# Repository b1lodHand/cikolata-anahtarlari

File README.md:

# cikolata anahtarlari
 cikulatli anahtarlar :d

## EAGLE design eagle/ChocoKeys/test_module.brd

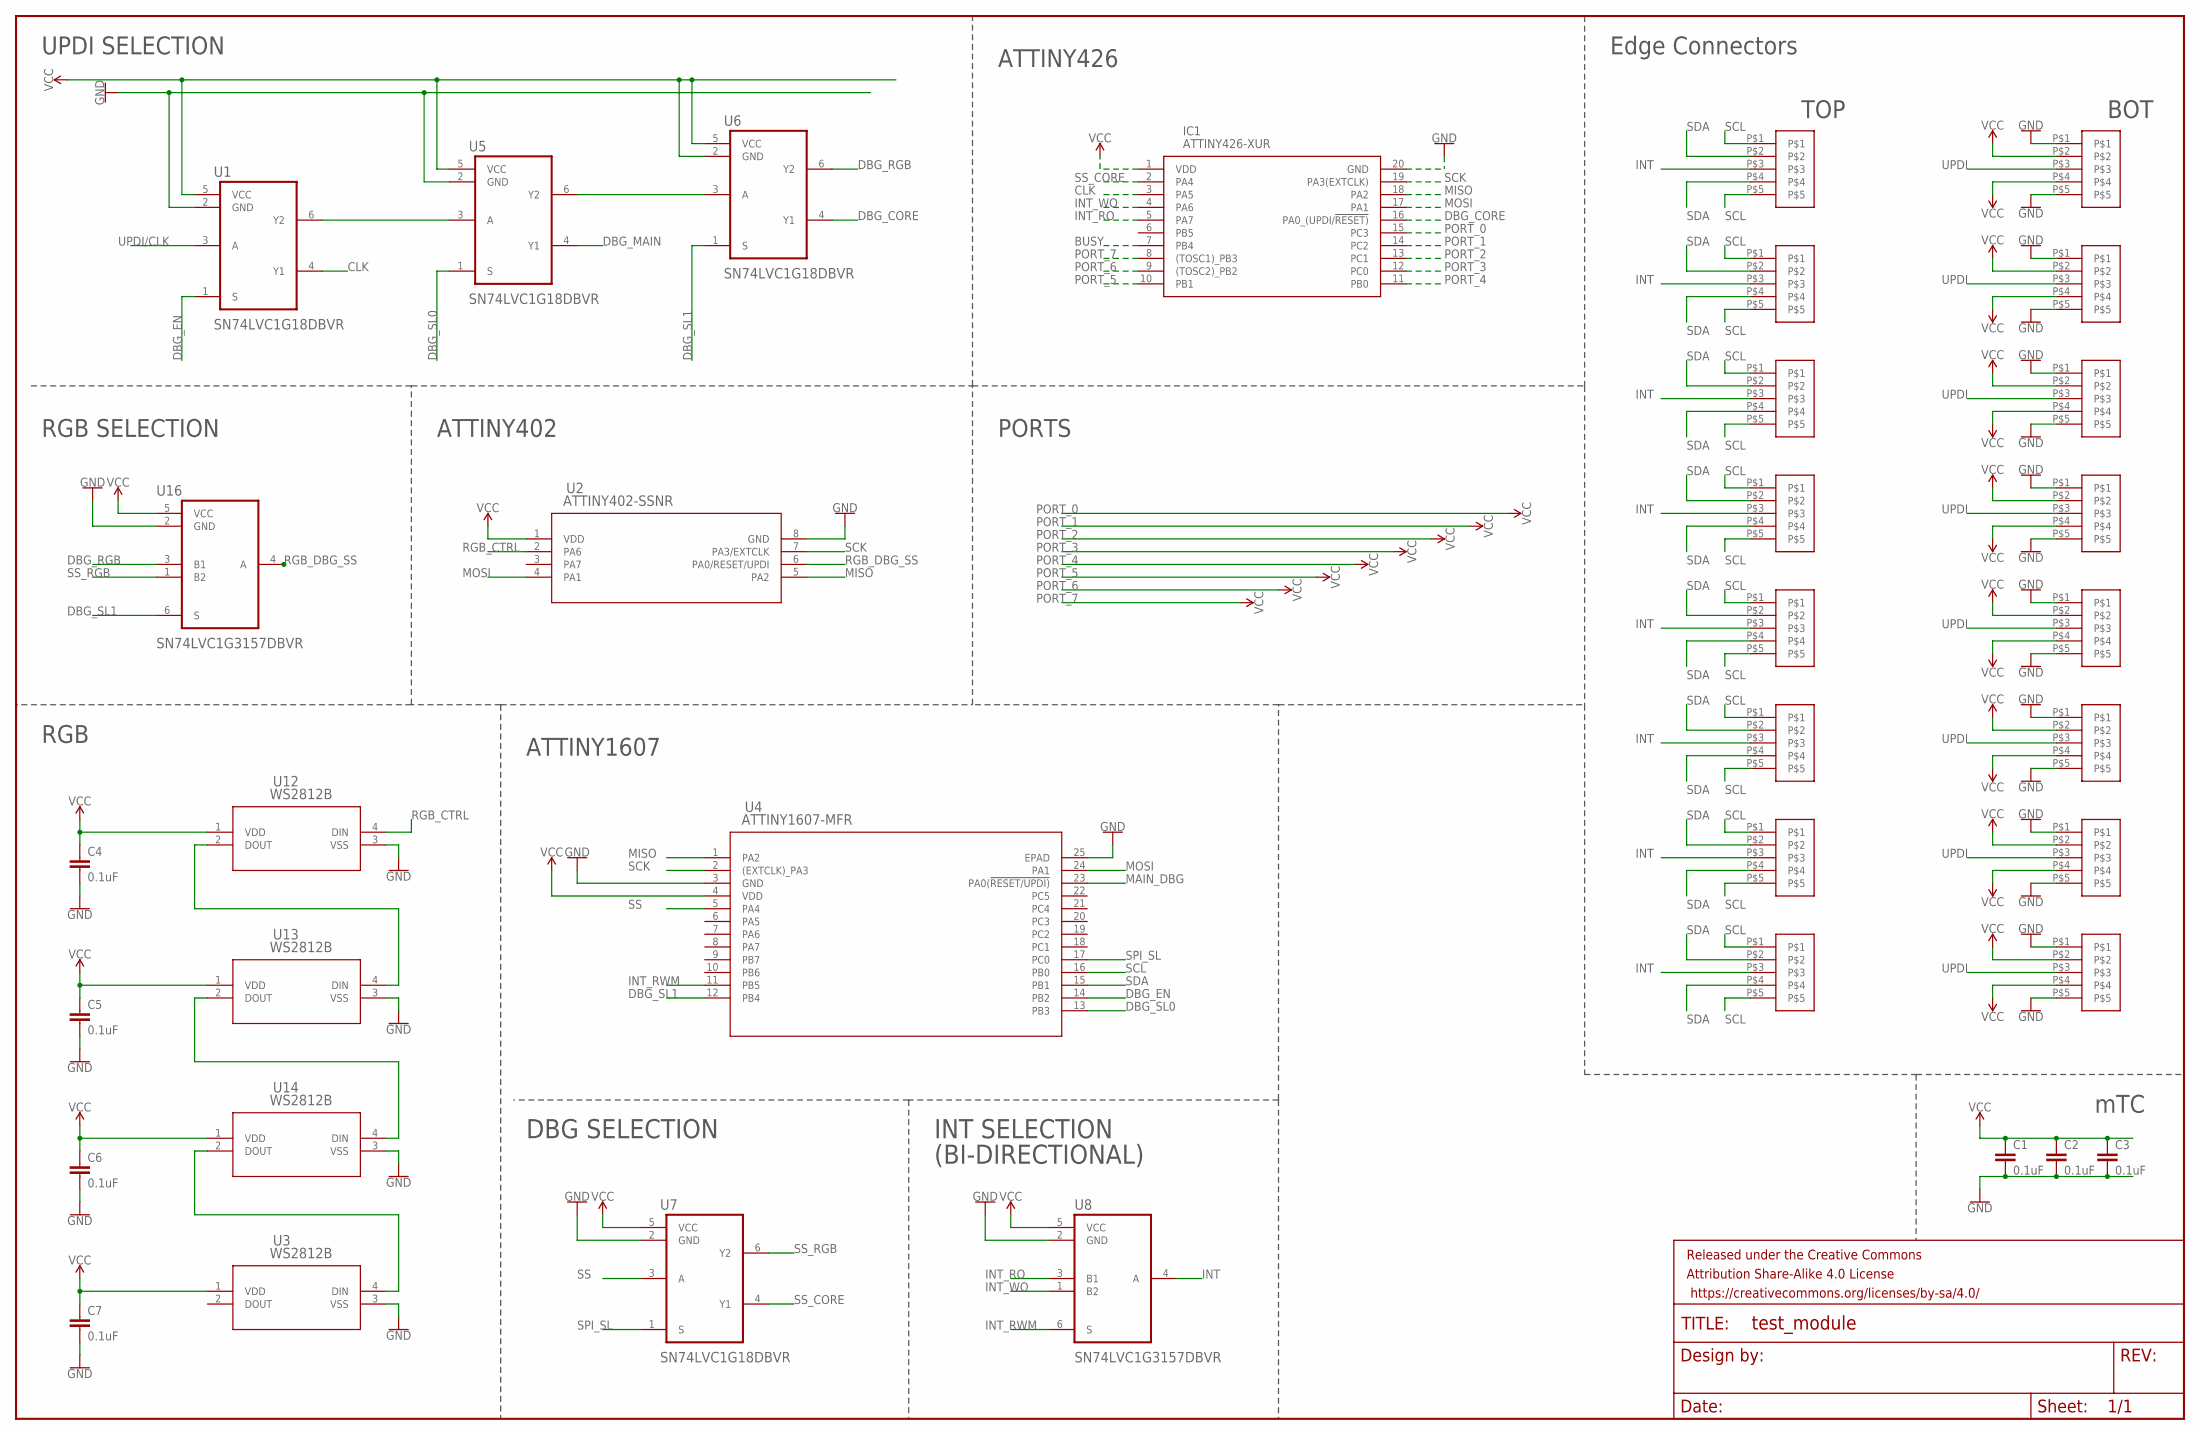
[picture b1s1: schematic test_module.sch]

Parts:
C1, C2, C3, C4, C5, C6, C7: 0.1uF; 0603
E1, E2, E3, E4, E5, E6, E7, E8, E9, E10, E11, E12, E13, E14, E15, E16: 5-PIN-EDGE-CONNECTOR
FRAME1: FRAME-LEDGER; CREATIVE_COMMONS
IC1: ATTINY426-XUR; SOP65P780X200-20N
U1, U5, U6, U7: SN74LVC1G18DBVR; SOT95P280X145-6N
U2: ATTINY402-SSNR; SOIC8_4P9X3P9MC_MCH
U3, U12, U13, U14: WS2812B; WS2812B_WDS
U4: ATTINY1607-MFR; QFN24_4X4_MCH
U8, U16: SN74LVC1G3157DBVR; SOT95P280X145-6N

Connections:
BUSY: IC1.7 (PB4)
CLK: IC1.3 (PA5), U1.4 (Y1)
DBG_CORE: IC1.16 (PA0_(UPDI/!RESET)), U6.4 (Y1)
DBG_EN: U1.1 (S), U4.14 (PB2)
DBG_MAIN: U5.4 (Y1)
DBG_RGB: U6.6 (Y2), U16.3 (B1)
DBG_SL0: U4.13 (PB3), U5.1 (S)
DBG_SL1: U4.12 (PB4), U6.1 (S), U16.6 (S)
GND: C1.2, C2.2, C3.2, C4.2, C5.2, C6.2, C7.2, E5.P$1, E5.P$5, E6.P$1, E6.P$5, E7.P$1, E7.P$5, E8.P$1, E8.P$5, E9.P$1, E9.P$5, E10.P$1, E10.P$5, E11.P$1, E11.P$5, E12.P$1, E12.P$5, IC1.20 (GND), U1.2 (GND), U2.8 (GND), U3.3 (VSS), U4.3 (GND), U4.25 (EPAD), U5.2 (GND), U7.2 (GND), U8.2 (GND), U12.3 (VSS), U13.3 (VSS), U14.3 (VSS), U16.2 (GND)
INT: E1.P$3, E2.P$3, E3.P$3, E4.P$3, E13.P$3, E14.P$3, E15.P$3, E16.P$3, U8.4 (A)
INT_RO: IC1.5 (PA7), U8.3 (B1)
INT_RWM: U4.11 (PB5), U8.6 (S)
INT_WO: IC1.4 (PA6), U8.1 (B2)
MAIN_DBG: U4.23 (PA0(!RESET/UPDI))
MISO: IC1.18 (PA2), U2.5 (PA2), U4.1 (PA2)
MOSI: IC1.17 (PA1), U2.4 (PA1), U4.24 (PA1)
unnamed: U12.2 (DOUT), U13.4 (DIN)
unnamed: U13.2 (DOUT), U14.4 (DIN)
unnamed: U3.4 (DIN), U14.2 (DOUT)
unnamed: U1.6 (Y2), U5.3 (A)
unnamed: U5.6 (Y2), U6.3 (A)
PORT_0: IC1.15 (PC3)
PORT_1: IC1.14 (PC2)
PORT_2: IC1.13 (PC1)
PORT_3: IC1.12 (PC0)
PORT_4: IC1.11 (PB0)
PORT_5: IC1.10 (PB1)
PORT_6: IC1.9 ((TOSC2)_PB2)
PORT_7: IC1.8 ((TOSC1)_PB3)
RGB_CTRL: U2.2 (PA6), U12.4 (DIN)
RGB_DBG_SS: U2.6 (PA0/RESET/UPDI), U16.4 (A)
SCK: IC1.19 (PA3(EXTCLK)), U2.7 (PA3/EXTCLK), U4.2 ((EXTCLK)_PA3)
SCL: E1.P$1, E1.P$5, E2.P$1, E2.P$5, E3.P$1, E3.P$5, E4.P$1, E4.P$5, E13.P$1, E13.P$5, E14.P$1, E14.P$5, E15.P$1, E15.P$5, E16.P$1, E16.P$5, U4.16 (PB0)
SDA: E1.P$2, E1.P$4, E2.P$2, E2.P$4, E3.P$2, E3.P$4, E4.P$2, E4.P$4, E13.P$2, E13.P$4, E14.P$2, E14.P$4, E15.P$2, E15.P$4, E16.P$2, E16.P$4, U4.15 (PB1)
SPI_SL: U4.17 (PC0), U7.1 (S)
SS: U4.5 (PA4), U7.3 (A)
SS_CORE: IC1.2 (PA4), U7.4 (Y1)
SS_RGB: U7.6 (Y2), U16.1 (B2)
UPDI: E5.P$3, E6.P$3, E7.P$3, E8.P$3, E9.P$3, E10.P$3, E11.P$3, E12.P$3
UPDI/CLK: U1.3 (A)
VCC: C1.1, C2.1, C3.1, C4.1, C5.1, C6.1, C7.1, E5.P$2, E5.P$4, E6.P$2, E6.P$4, E7.P$2, E7.P$4, E8.P$2, E8.P$4, E9.P$2, E9.P$4, E10.P$2, E10.P$4, E11.P$2, E11.P$4, E12.P$2, E12.P$4, IC1.1 (VDD), U1.5 (VCC), U2.1 (VDD), U3.1 (VDD), U4.4 (VDD), U5.5 (VCC), U6.2 (GND), U6.5 (VCC), U7.5 (VCC), U8.5 (VCC), U12.1 (VDD), U13.1 (VDD), U14.1 (VDD), U16.5 (VCC)

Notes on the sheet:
mTC
TOP
BOT
Edge Connectors
RGB
UPDI SELECTION
RGB SELECTION
ATTINY1607
ATTINY402
DBG SELECTION
INT SELECTION
(BI-DIRECTIONAL)
ATTINY426
PORTS

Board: 2 copper layers, 37 parts (12 on the bottom side), 29 nets, no tracks yet.

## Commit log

2024-09-07 initiated test GUI app
2024-09-21 fetch
2024-09-21 added eagle (manual)
2024-09-23 32.09.2024
    update eagle

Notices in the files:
parts and their libraries:
SparkFun-Aesthetics: Licensing: Creative Commons ShareAlike 4.0 International - https://creativecommons.org/licenses/by-sa/4.0
SparkFun-Aesthetics: Released under the Creative Commons Attribution Share-Alike 4.0 License
SparkFun-Aesthetics: https://creativecommons.org/licenses/by-sa/4.0
